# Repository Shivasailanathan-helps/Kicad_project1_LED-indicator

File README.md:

## Overview
This repository contains my **very first Printed Circuit Board (PCB) design project**, built completely from scratch using **KiCad EDA**. 

This project serves as a hands-on milestone to transition into professional hardware engineering and establish an end-to-end Electronic Design Automation (EDA) workflow—spanning schematic capture, footprint assignment, 2-layer PCB layout routing, and design rule verification.

---

## Technical Highlights & Workflow
* **Schematic Design:** Created clean circuit schematics with proper power/ground routing, component value selection, and netlist generation.
* **Component Footprint Assignment:** Mapped symbols to standard surface-mount (SMD) / through-hole (TTH) component footprints.
* **PCB Layout & Routing:**
  * Designed a compact 2-layer PCB layout.
  * Optimized component placement for minimal trace lengths and noise.
  * Added pour areas / ground planes and clear silkscreen text for assembly clarity.
* **Design Rule Check (DRC):** Fully verified layout constraints; passed with **0 DRC errors and 0 warnings**.
* **Version Control:** Managed and tracked hardware source files using Git and GitHub.

---
## Final Outputs

## Project Structure
```text
├── Project 1.kicad_pro    # KiCad project file
├── Project 1.kicad_sch    # Schematic diagram
├── Project 1.kicad_pcb    # PCB board layout
├── KiCAD_Project1.png     # Rendered layout preview
└── Netlist files_project1.net

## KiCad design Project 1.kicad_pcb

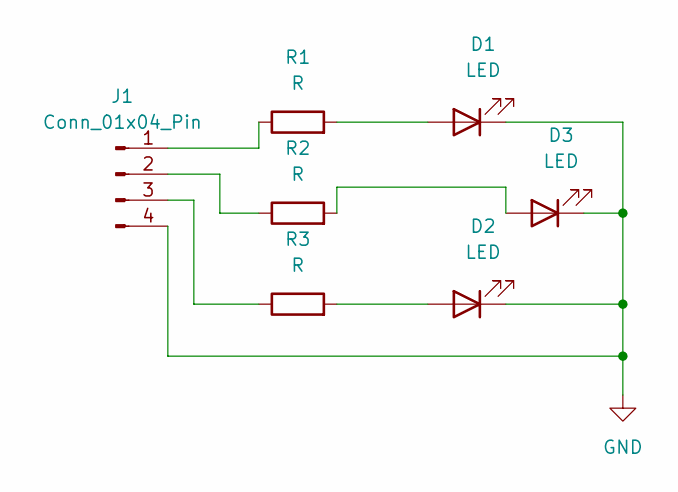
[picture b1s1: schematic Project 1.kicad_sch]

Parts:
D1, D2, D3: LED; LED_D5.0mm_FlatTop
J1: Conn_01x04_Pin; PinHeader_1x04_P2.54mm_Vertical
R1, R2, R3: R; R_Axial_DIN0204_L3.6mm_D1.6mm_P5.08mm_Horizontal

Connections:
GND: D1.1 (K), D2.1 (K), D3.1 (K), J1.4
unnamed: D1.2 (A), R1.2
unnamed: D2.2 (A), R3.2
unnamed: D3.2 (A), R2.2
unnamed: J1.1, R1.1
unnamed: J1.2, R2.1
unnamed: J1.3, R3.1

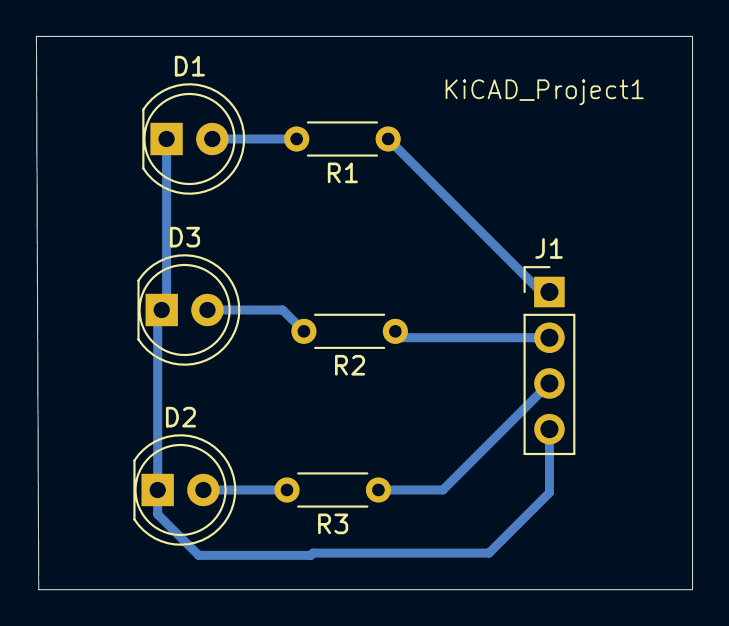
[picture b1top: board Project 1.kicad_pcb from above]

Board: 2 copper layers, 36.4 x 30.7 mm, 7 parts (0 on the bottom side), 7 nets.
